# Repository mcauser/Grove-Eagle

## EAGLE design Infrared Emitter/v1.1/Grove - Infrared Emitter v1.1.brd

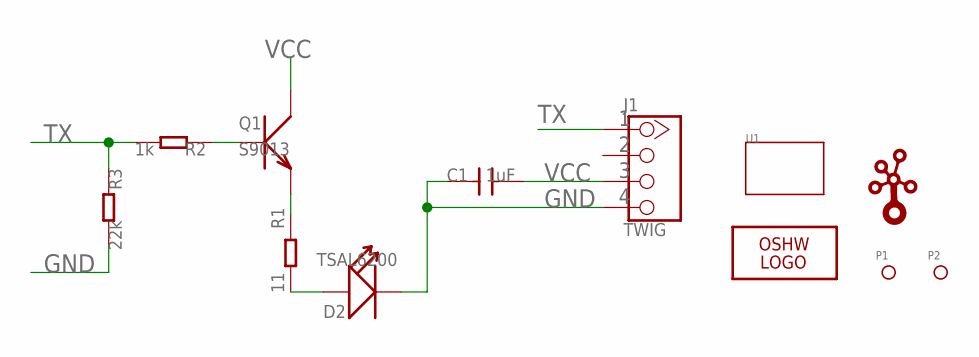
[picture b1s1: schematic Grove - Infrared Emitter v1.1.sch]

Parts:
C1: 1uF; 0805
D2: TSAL6200; 2P-LEADED-ROUND-2.54-R3.0
J1: TWIG; 4P-LEADED-2.0
LOGO1: LOGO-OSHW-FILLX0150-NT; OSHW_FILLX150_NOTEXT
P1, P2: PAD-MARK; ROUND-MARK-1.0
Q1: S9013; SOT23
R1: 11; 0805
R2: 1k; 0603
R3: 22k; 0603
U1: TWIG-1U; 1U-DIM-W/-DRILL
U$1: LOGO-TWIGTWIGLOGO_SMALL; TWIGLOGO_SMALL

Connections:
GND: C1.1, D2.-, J1.4, R3.2
unnamed: Q1.1 (B), R2.1
unnamed: Q1.2 (E), R1.1
unnamed: D2.+, R1.2
TX: J1.1, R2.2, R3.1
VCC: C1.2, J1.3, Q1.3 (C)

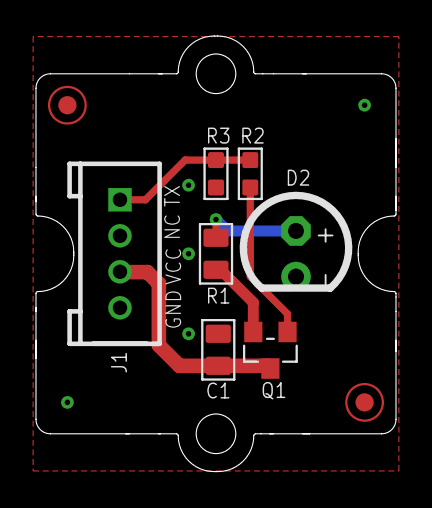
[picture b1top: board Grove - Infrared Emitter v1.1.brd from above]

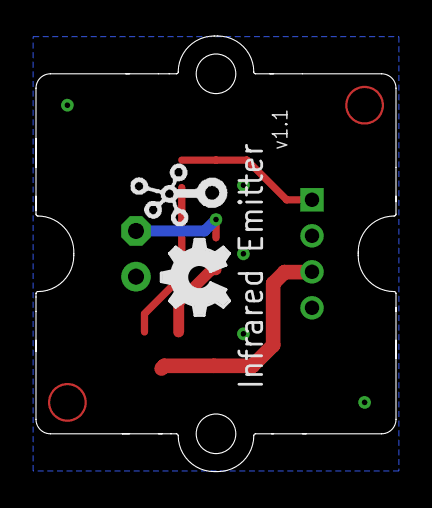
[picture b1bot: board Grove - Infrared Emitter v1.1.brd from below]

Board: 2 copper layers, 20.0 x 24.2 mm, 12 parts (2 on the bottom side), 6 nets.

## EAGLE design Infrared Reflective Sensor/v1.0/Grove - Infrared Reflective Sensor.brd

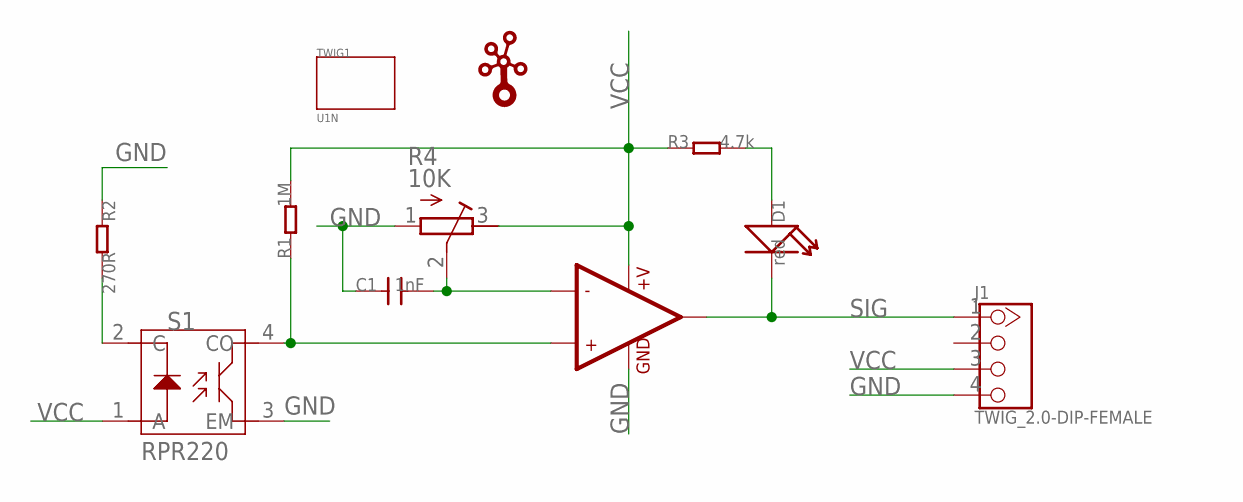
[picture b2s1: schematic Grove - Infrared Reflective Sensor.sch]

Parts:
C1: 1nF; 0603
D1: red; LED0603
J1: TWIG_2.0-DIP-FEMALE; 2.0_1X4
R1: 1M; 0603_S
R2: 270R; 0603_S
R3: 4.7k; 0603_S
R4: 10K; RTRIM3214W
S1: RPR220; 4P-6.4X4.9X6.5H
TWIG1: U1N
U1: 002-LMV358; SO08
U$2: TWIGLOGOTWIGLOGO_SMALL; TWIGLOGO_SMALL

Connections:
GND: C1.1, J1.4, R2.1, R4.1 (E), S1.3 (EM), U1.4 (GND)
unnamed: C1.2, R4.2 (S), U1.2 (-IN1)
unnamed: R1.1, S1.4 (CO), U1.3 (+IN1)
unnamed: R2.2, S1.2 (C)
unnamed: D1.1 (+), R3.2
SIG: D1.2 (-), J1.1, U1.1 (OUT1)
VCC: J1.3, R1.2, R3.1, R4.3 (A), S1.1 (A), U1.8 (+V)

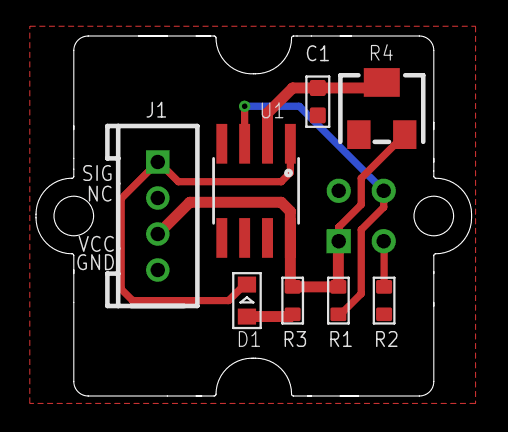
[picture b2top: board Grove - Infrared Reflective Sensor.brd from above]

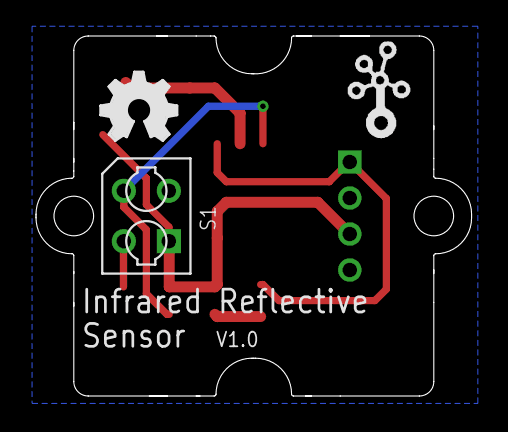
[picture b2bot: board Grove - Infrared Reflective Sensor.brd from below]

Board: 2 copper layers, 24.2 x 20.0 mm, 12 parts (3 on the bottom side), 7 nets.

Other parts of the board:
U$1: OSHW_FILLX150_NOTEXT

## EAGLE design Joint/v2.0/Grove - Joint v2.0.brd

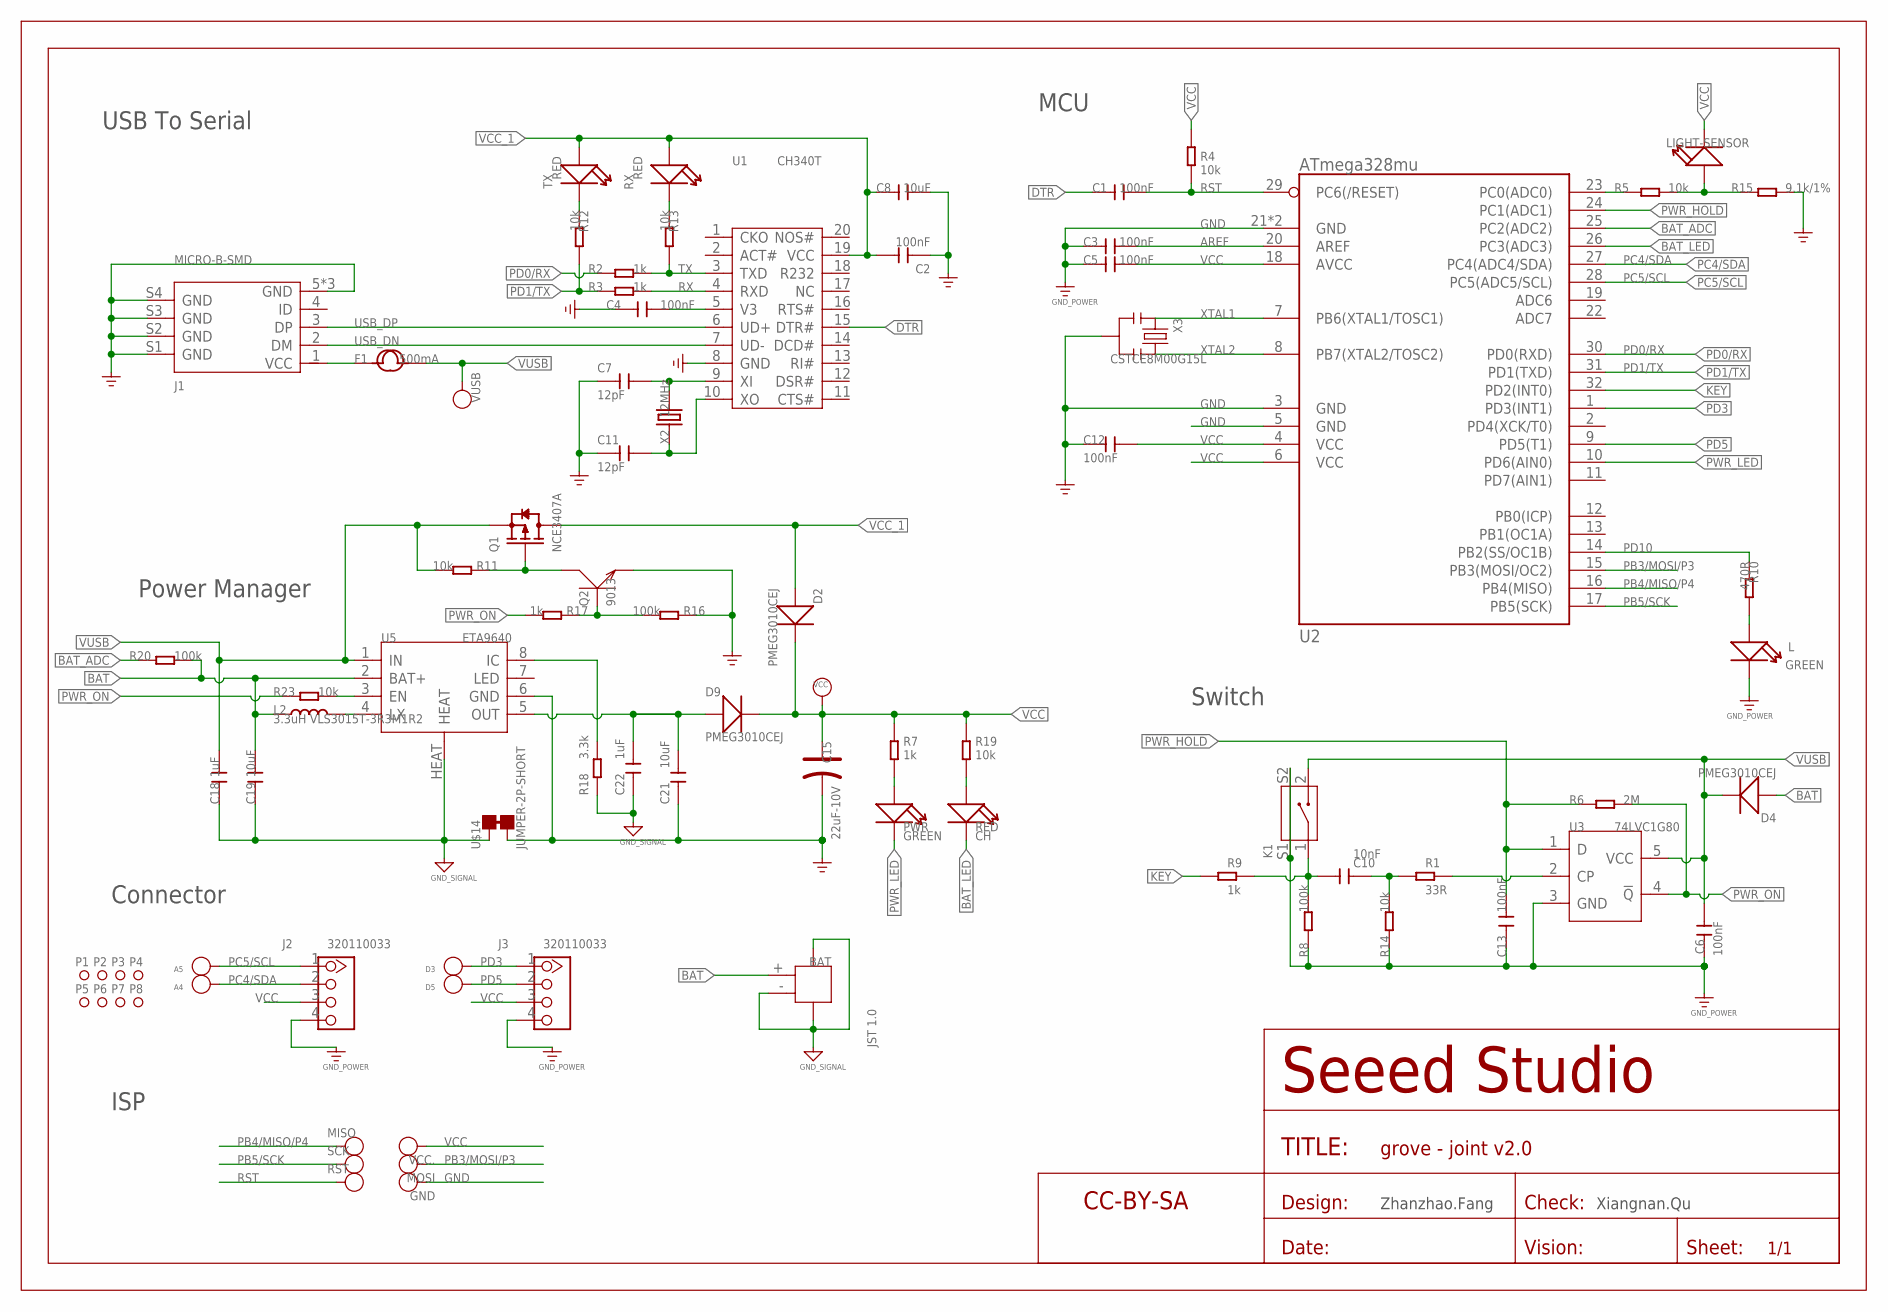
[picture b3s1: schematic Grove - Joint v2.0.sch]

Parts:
A4, A5: DNP; TP_4545
BAT: JST 1.0; 2P-SMD-1.0
C1, C2, C3, C4, C5, C6, C12, C13: 100nF; C0402
C7, C11: 12pF; C0402
C8, C19, C21: 10uF; C0805
C10: 10nF; C0402
C15: 22uF-10V; AVX-A
C18: 1uF; C0805
C22: 1uF; C0603
CH: RED; LED-0402
D2, D4, D9: PMEG3010CEJ; SOD-323
D3: DNP; TP-D45MIL
D5: DNP; TP_4545
F1: 500mA; F1206
GND: DNP; TP-D45MIL
J1: MICRO-B-SMD; 5+4P-SMD-0.65-B
J2, J3: 320110033; 4P-2.0
K1: 311020023; 4P-SMD-L7.0*W3.5*H3.5MM-90D
L: GREEN; LED-0402
L2: 3.3uH VLS3015T-3R3M1R2; L3015
LIGHT-SENSOR: light_sensor; LED-0805
MISO: DNP; TP-D45MIL
MOSI: DNP; TP-D45MIL
P1, P2, P3, P4, P5, P6, P7, P8: PAD-MARK'ANNULAR'; ROUND-MARK-1.0
PWR: GREEN; LED-0402
Q1: NCE3407A; SOT-23
Q2: 9013; SOT-323
R1: 33R; R0402
R2, R3, R7, R9, R17: 1k; R0402
R4, R5, R11, R12, R13, R14, R19, R23: 10k; R0402
R6: 2M; R0402
R8, R16, R20: 100k; R0402
R10: 470R; R0402
R15: 9.1k/1%; R0402
R18: 3.3k; R0402
RST: DNP; TP-D45MIL
RX: RED; LED-0402
SCK: DNP; TP-D45MIL
TX: RED; LED-0402
U1: CH340T; SSOP20
U2: ATmega328mu; MLF32X-W/HEAT
U3: 74LVC1G80; SOT-753
U5: ETA9640; SOP8-W/HEAT
U$4: SEEEDSTUDIO-OPEN-SCH-FRAME; SEEEDSTUDIO-PCB-FRAME
U$14: JUMPER-2P-SHORT; 2P-SMD-SHORT
VCC, VCC.: NC; TP-D45MIL
VUSB: PAD-TEST-POINT'4545'; TP-D45MIL
X2: 12MHz; 2P-SMD-L5.0XW3.2MM
X3: CSTCE8M00G15L; 3P-SMD-L3.6*W1.3MM

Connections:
!PWR_HOLD: C13.2, R6.1, U2.24 (PC1(ADC1)), U3.1 (D)
AGND: BAT.3, BAT.4, BAT.- (2), C18.1, C19.1, C22.1, R18.2, U5.HEAT, U$14.1
AREF: C3.2, U2.20 (AREF)
BAT: BAT.+ (1), C19.2, D4.+, L2.1, R20.2, U5.2 (BAT+)
BAT_ADC: R20.1, U2.25 (PC2(ADC2))
BAT_LED: CH.-, U2.26 (PC3(ADC3))
BOOST: C21.2, C22.2, D9.+, U5.5 (OUT)
DTR: C1.1, U1.15 (DTR#)
GND: C2.1, C3.1, C4.2, C5.1, C6.2, C7.1, C8.2, C11.1, C12.1, C13.1, C15.-, C21.1, GND.T, J1.5 (GND), J1.S1 (GND), J1.S2 (GND), J1.S3 (GND), J1.S4 (GND), J1.S5 (GND), J1.S6 (GND), J2.4, J3.4, K1.S1, K1.S2, L.-, Q2.2 (E), R8.1, R14.1, R15.2, R16.2, U1.8 (GND), U2.3 (GND), U2.5 (GND), U2.21 (GND), U2.HEAT (GND), U3.3 (GND), U5.6 (GND), U$14.2, X3.2
KEY: R9.1, U2.32 (PD2(INT0))
unnamed: C10.1, R1.1, R14.2
unnamed: L.+, R10.2
unnamed: LIGHT-SENSOR.+, R5.2, R15.1
unnamed: CH.+, R19.1
unnamed: C10.2, K1.1, R8.2, R9.2
unnamed: R5.1, U2.23 (PC0(ADC0))
unnamed: R23.2, U5.3 (EN)
unnamed: R12.1, TX.-
unnamed: R13.1, RX.-
unnamed: C7.2, U1.9 (XI), X2.2
unnamed: R1.2, U3.2 (CP)
unnamed: Q1.1 (G), Q2.3 (C), R11.2
unnamed: PWR.+, R7.2
unnamed: C11.2, U1.10 (XO), X2.1
unnamed: Q2.1 (B), R16.1, R17.2
unnamed: R18.1, U5.8 (IC)
unnamed: F1.1, J1.1 (VCC)
unnamed: L2.2, U5.4 (LX)
PB3/MOSI/P3: MOSI.T, U2.15 (PB3(MOSI/OC2))
PB4/MISO/P4: MISO.T, U2.16 (PB4(MISO))
PB5/SCK: SCK.T, U2.17 (PB5(SCK))
PC4/SDA: A4.T, J2.2, U2.27 (PC4(ADC4/SDA))
PC5/SCL: A5.T, J2.1, U2.28 (PC5(ADC5/SCL))
PD0/RX: R2.1, U2.30 (PD0(RXD))
PD1/TX: R3.1, R12.2, U2.31 (PD1(TXD))
PD3: D3.T, J3.1, U2.1 (PD3(INT1))
PD5: D5.T, J3.2, U2.9 (PD5(T1))
PD10: R10.1, U2.14 (PB2(SS/OC1B))
PWR_LED: PWR.-, U2.10 (PD6(AIN0))
PWR_ON: R6.2, R17.1, R23.1, U3.4 (!Q)
RST: C1.2, R4.1, RST.T, U2.29 (PC6(/RESET))
RX: R3.2, U1.4 (RXD)
TX: R2.2, R13.2, U1.3 (TXD)
USB_DN: J1.2 (DM), U1.7 (UD-)
USB_DP: J1.3 (DP), U1.6 (UD+)
V3: C4.1, U1.5 (V3)
VCC: C5.2, C12.2, C15.+, D2.-, D9.-, J2.3, J3.3, LIGHT-SENSOR.-, R4.2, R7.1, R19.2, U2.4 (VCC), U2.6 (VCC), U2.18 (AVCC), VCC.T, VCC..T
VCC_1: C2.2, C8.1, D2.+, Q1.3 (D), RX.+, TX.+, U1.19 (VCC)
VUSB: C6.1, C18.2, D4.-, F1.2, K1.2, Q1.2 (S), R11.1, U3.5 (VCC), U5.1 (IN), VUSB.T
XTAL1: U2.7 (PB6(XTAL1/TOSC1)), X3.1
XTAL2: U2.8 (PB7(XTAL2/TOSC2)), X3.3

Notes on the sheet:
Zhanzhao.Fang
USB To Serial
MCU
Connector
Switch
Power Manager
ISP
Xiangnan.Qu

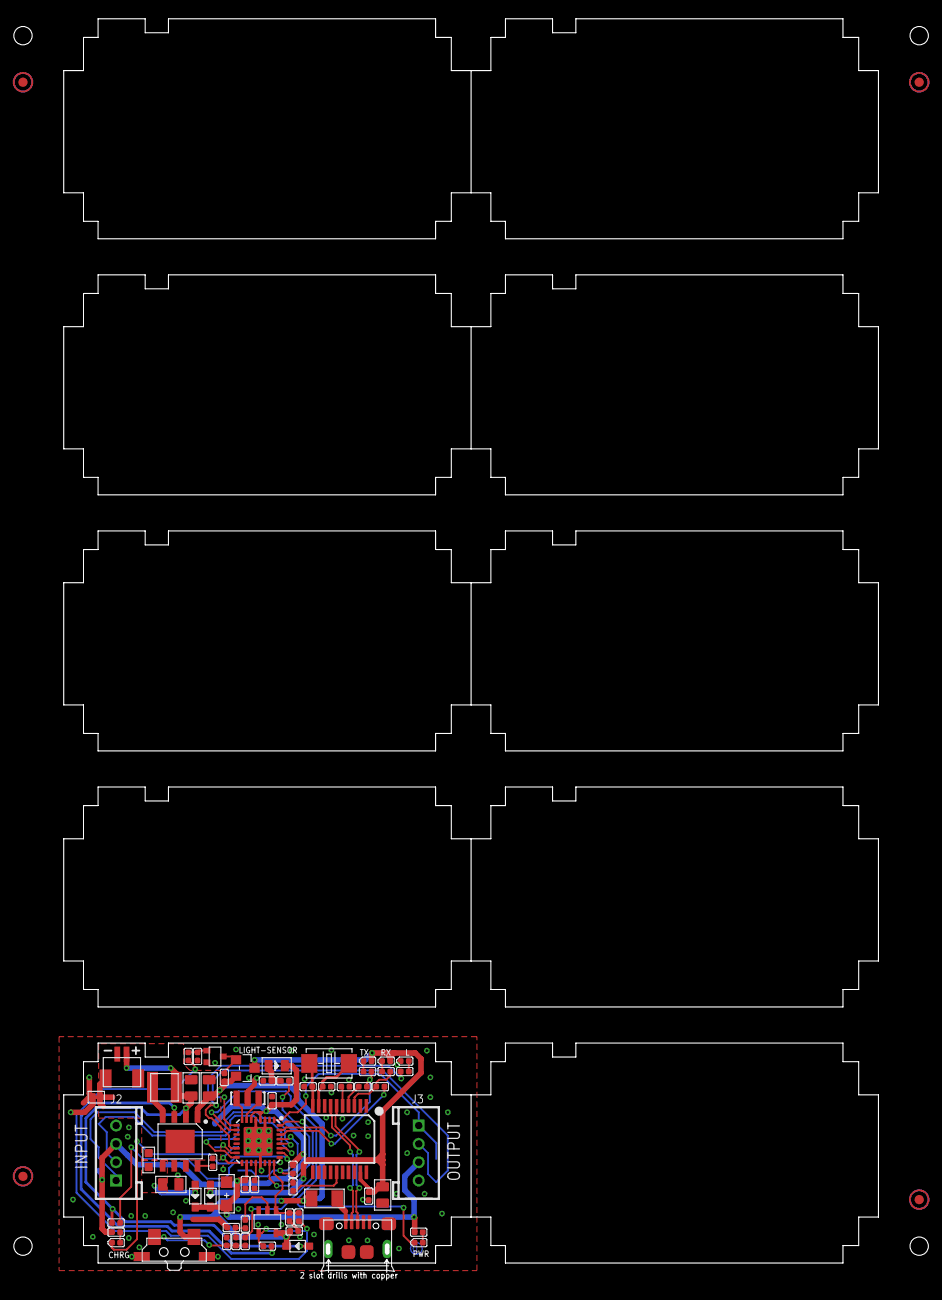
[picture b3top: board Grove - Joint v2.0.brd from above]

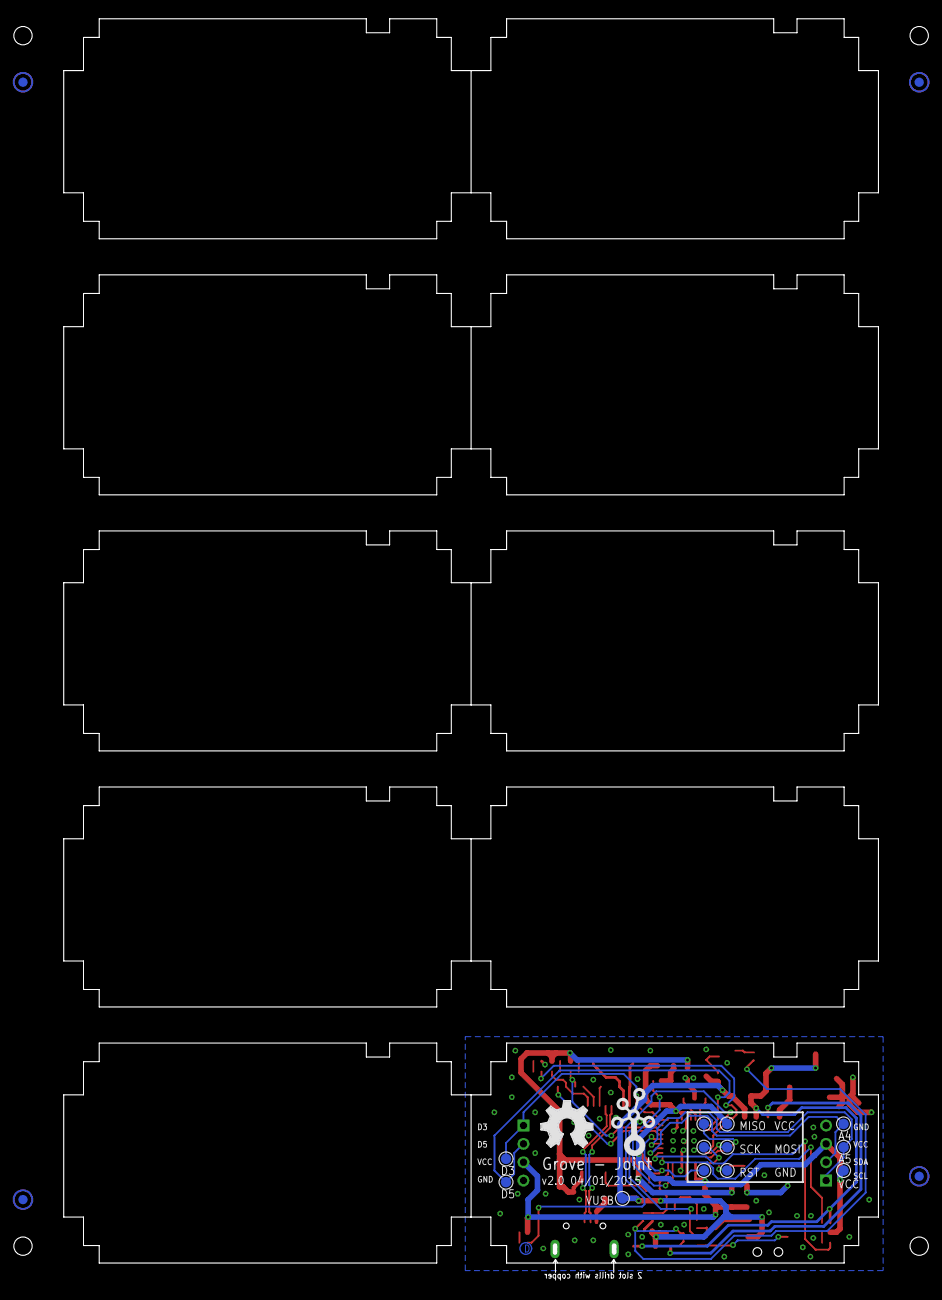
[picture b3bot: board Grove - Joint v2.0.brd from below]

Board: 2 copper layers, 88.9 x 24.0 mm, 86 parts (18 on the bottom side), 51 nets.

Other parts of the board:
U$2: OSHW_FILLX200_NOTEXT
U$3: TWIGLOGO

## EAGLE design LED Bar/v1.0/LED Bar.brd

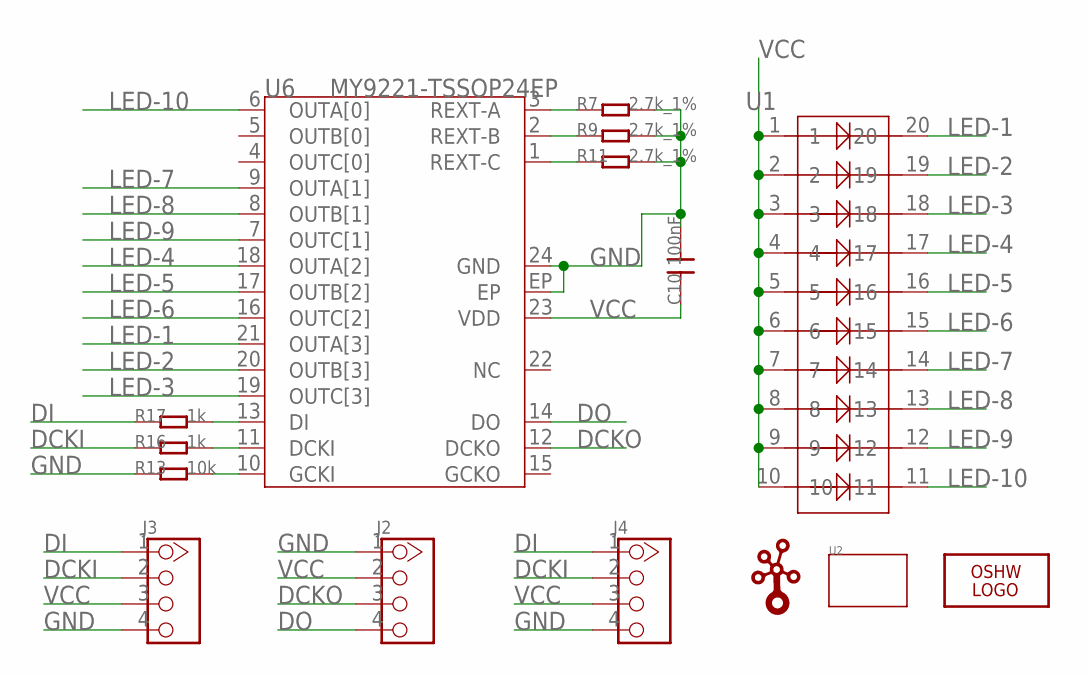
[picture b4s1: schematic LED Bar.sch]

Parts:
C10: 100nF; 0603
J2: HEADER-4P-90D; 4P-2.54-90
J3: HEADER-4P'2.54-90D-FEMALE'; 4P-2.54-90D-FEMALE
J4: TWIG-4P-2.0-2.0; 4P-2.0
LOGO1: LOGO-OSHW-FILLX0150-NT; OSHW_FILLX150_NOTEXT
R7, R9, R11: 2.7k_1%; 0603
R13: 10k; 0603
R16, R17: 1k; 0603
U1: LED-20P; 20P-DIP-2.54-25.5X10.1X8.4H
U2: TWIG-2U; 2U-DIM-W/-DRILL
U6: MY9221-TSSOP24EP; TSSOP24EP
U$1: LOGO-TWIGTWIGLOGO_SMALL; TWIGLOGO_SMALL

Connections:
DCKI: J3.2, J4.2, R16.1
DCKO: J2.3, U6.12 (DCKO)
DI: J3.1, J4.1, R17.1
DO: J2.4, U6.14 (DO)
GND: C10.2, J2.1, J3.4, J4.4, R7.2, R9.2, R11.2, R13.1, U6.24 (GND), U6.EP
LED-1: U1.20, U6.21 (OUTA[3])
LED-2: U1.19, U6.20 (OUTB[3])
LED-3: U1.18, U6.19 (OUTC[3])
LED-4: U1.17, U6.18 (OUTA[2])
LED-5: U1.16, U6.17 (OUTB[2])
LED-6: U1.15, U6.16 (OUTC[2])
LED-7: U1.14, U6.9 (OUTA[1])
LED-8: U1.13, U6.8 (OUTB[1])
LED-9: U1.12, U6.7 (OUTC[1])
LED-10: U1.11, U6.6 (OUTA[0])
unnamed: R17.2, U6.13 (DI)
unnamed: R16.2, U6.11 (DCKI)
unnamed: R13.2, U6.10 (GCKI)
unnamed: R11.1, U6.1 (REXT-C)
unnamed: R9.1, U6.2 (REXT-B)
unnamed: R7.1, U6.3 (REXT-A)
VCC: C10.1, J2.2, J3.3, J4.3, U1.1, U1.2, U1.3, U1.4, U1.5, U1.6, U1.7, U1.8, U1.9, U1.10, U6.23 (VDD)

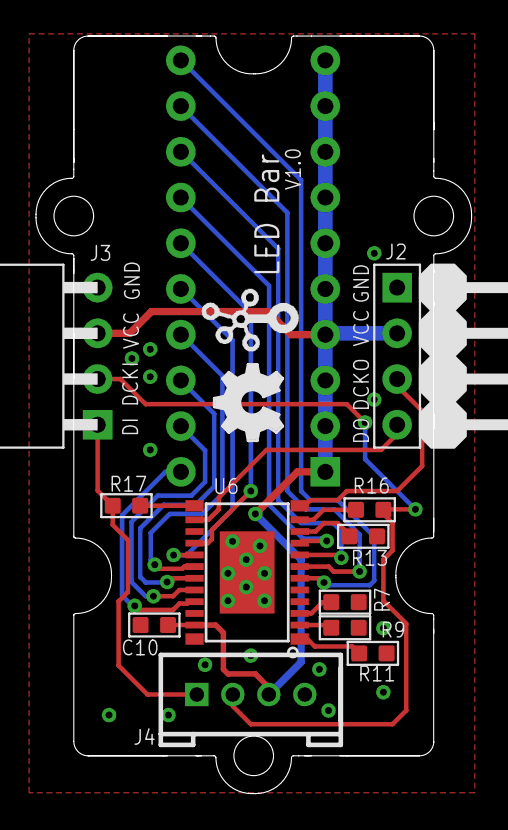
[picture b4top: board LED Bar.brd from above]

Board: 2 copper layers, 24.2 x 42.1 mm, 15 parts (1 on the bottom side), 22 nets.

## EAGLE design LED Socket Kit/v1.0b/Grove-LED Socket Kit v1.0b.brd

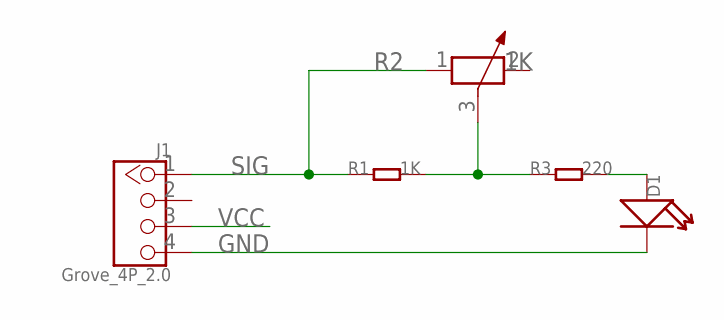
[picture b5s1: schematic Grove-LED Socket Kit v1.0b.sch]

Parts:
D1: LED-6MM; LED-2P-2.54-6MM
J1: Grove_4P_2.0; 2.0_1X4
R1: 1K; 0603
R2: 1K; 3P-SQUA-7X6.8
R3: 220; 0603

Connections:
GND: D1.-, J1.4
unnamed: R1.2, R2.3, R3.1
unnamed: D1.+, R3.2
SIG: J1.1, R1.1, R2.1
VCC: J1.3

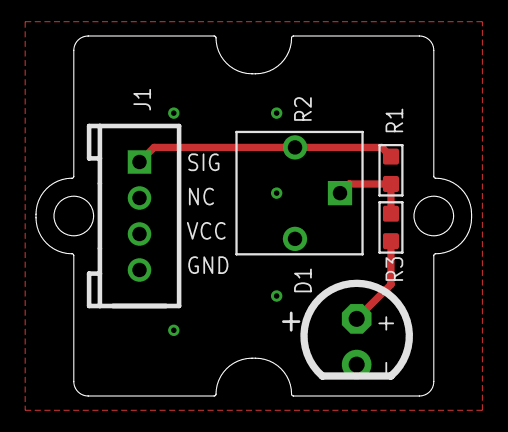
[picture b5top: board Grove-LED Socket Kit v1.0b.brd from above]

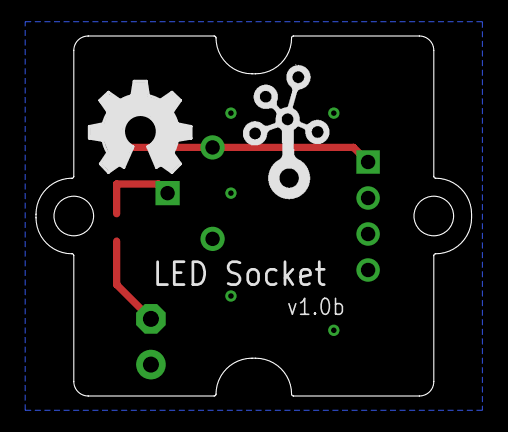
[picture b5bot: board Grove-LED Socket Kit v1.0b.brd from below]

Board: 2 copper layers, 24.2 x 20.0 mm, 8 parts (2 on the bottom side), 4 nets.

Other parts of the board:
U$2: 1U-DIM-W/-DRILL
U$3: OSHW_FILLX200_NOTEXT
U$4: TWIGLOGO

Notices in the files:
parts and their libraries:
moudle-new: This work is licensed under the Creative Commons Attribution 4.0 International License.
To view a copy of this license,visit:
http://creativecommons.org/licenses/by-sa/4.0
moudle-new: CC-BY-SA
